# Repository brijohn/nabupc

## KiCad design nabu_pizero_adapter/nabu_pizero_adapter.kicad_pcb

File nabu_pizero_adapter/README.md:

# Description
This is a carrier board designed for a Raspberry Pi Zero W. It was made to fit in the empty case of an nabu network cable adapter and host a NABU Network Emulator allowing your nabu to request and load software.

The uses a MAX3070 to produce a RS422 signal from the PI's TTL UART and has a super capacitor based UPS to allow the pi time to cleanly shutdown in the event of a power loss. It has has a header that the front panel LEDS can be connected to and then controlled by the PI.

# Setup
In addition to this board you will also need a Raspberry PI Zero W. Though a suitable alternative is the bananapi M2 Zero, which has the same pinout and form factor, it also includes a U.FL connector for an external antenna, whereas the raspberry pi needs to modified.

The external antenna can be mounted in the existing F type connector hole in the back of the case, though since an SMA connector is smaller then an F type you will need a couple of washers on each side of the antenna's SMA connector to mount it.

The code used with the ATTiny85 to monitor the power status and report it to the PI over I2C was written by Scott M. Baker and can be found at https://github.com/sbelectronics/ups/.

# BOM

|         Item        |     Reference     | Quantity |             Digikey              |
|---------------------|-------------------|----------|----------------------------------|
|  0.1uf Capacitor    |  C3, C4, C5, C6   |     4    |          490-9197-1-ND           |
| 50F Super-capacitor |      C1, C2       |     2    |          1182-1051-ND            |
|    1N5820 Diode     |      D1, D3       |     2    |      112-1N5820-E3/73CT-ND       |
|   5.6V Zener Diode  |        D2         |     1    |         1N4734AFSCT-ND           |
|   5.1V Zener Diode  |        D4         |     1    |         1N4733AFSCT-ND           |
|      1A Fuse        |        F1         |     1    |             F2313-ND             |
|  Single Row Headers |    J3, J4, J5     |     1    |          S1012EC-40-ND           |
|      5-pin DIN      |        J2         |     1    |            CP-2350-ND            |
|    180 Resistor     |        R1         |     1    |     13-MFR-25FTE52-180RCT-ND     |
|    220 Resistor     | R9, R10, R11, R12 |     4    |             220QBK-ND            |
|    1k Resistor      |      R3, R4       |     2    |             1.0KQBK-ND           |
|   7.5k Resistor     |      R6, R8       |     2    |             7.5KQBK-ND           |
|   10k Resistor      |      R5, R7       |     2    |      13-CFR-25JT-52-10KCT-ND     |
|   2.2 3W Resistor   |        R2         |     1    |            A138434CT-ND          |
|      ATtiny85V      |        U3         |     1    |         ATTINY85V-10PU-ND        |
|       MAX3070       |        U1         |     1    |          MAX3070EEPD+-ND         |
|   Shunt Regulator   |      U5, U6       |     2    |            296-50325-ND          |
|       ULN2803A      |        U2         |     1    |            497-2356-5-ND         |
|      5V Step-Up     |        U4         |     1    | 2183-2891-ND, S7037-ND, S7038-ND |

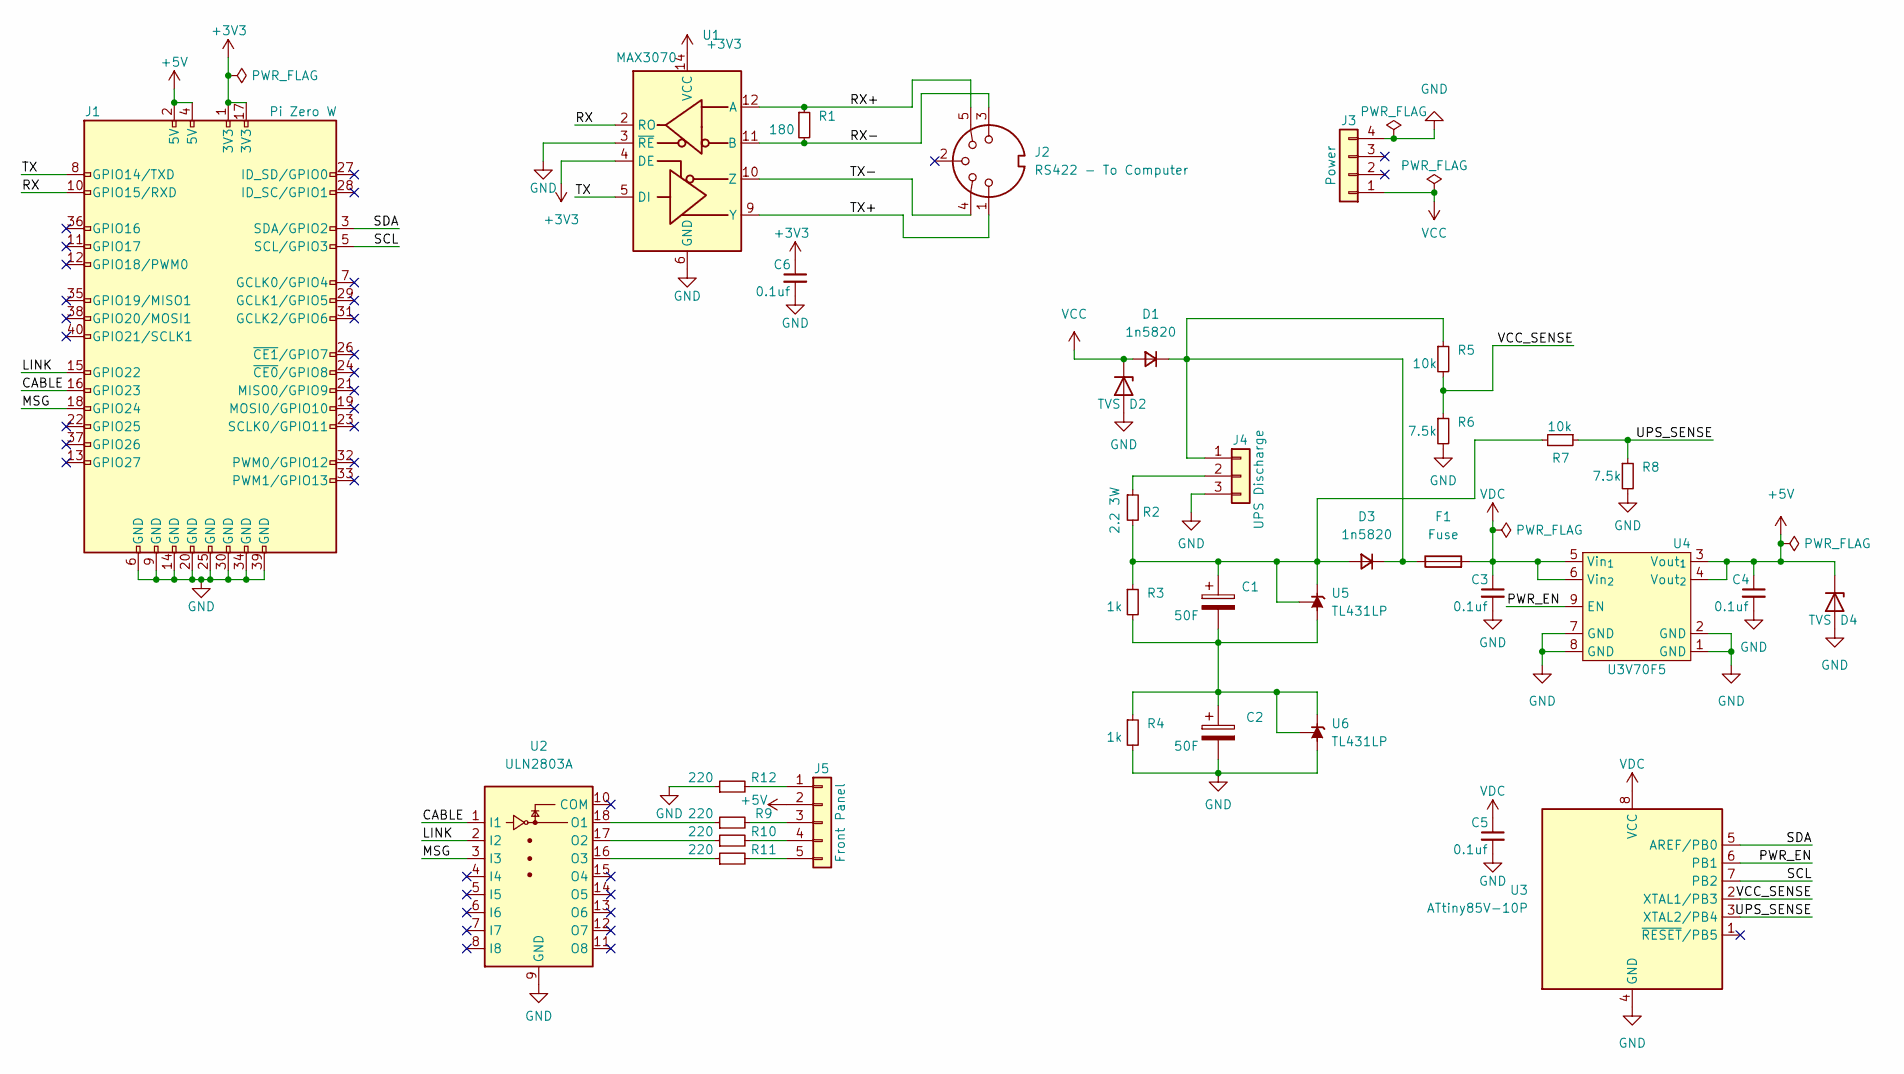
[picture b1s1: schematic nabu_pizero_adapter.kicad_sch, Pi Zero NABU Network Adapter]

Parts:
C1, C2: 50F; CP_Radial_D18.0mm_P7.50mm; Digi-Key 1182-1051-ND
C3, C4, C5, C6: 0.1uf; C_Disc_D5.0mm_W2.5mm_P2.50mm; Digi-Key 490-9197-1-ND
D1, D3: 1n5820; D_DO-201AD_P15.24mm_Horizontal; Digi-Key 112-1N5820-E3/73CT-ND
D2: TVS; D_DO-41_SOD81_P10.16mm_Horizontal; Digi-Key 1N4734AFSCT-ND
D4: TVS; D_DO-41_SOD81_P10.16mm_Horizontal; Digi-Key 1N4733AFSCT-ND
F1: Fuse; 0251001.MXL; Digi-Key F2313-ND
J1: Pi Zero W; Raspberry_Pi_Zero_Socketed_THT_MountingHoles; Digi-Key 1988-1063-ND
J2: RS422 - To Computer; CUI_SDS-50J; Digi-Key CP-2350-ND
J3: Power; PinHeader_1x04_P2.54mm_Vertical; Digi-Key S1012EC-40-ND
J4: UPS Discharge; PinHeader_1x03_P2.54mm_Vertical
J5: Front Panel; PinHeader_1x05_P2.54mm_Vertical
R1: 180; R_Axial_DIN0207_L6.3mm_D2.5mm_P10.16mm_Horizontal; Digi-Key 13-MFR-25FTE52-180RCT-ND
R2: 2.2 3W; R_Axial_DIN0516_L15.5mm_D5.0mm_P20.32mm_Horizontal; Digi-Key A138434CT-ND
R3, R4: 1k; R_Axial_DIN0207_L6.3mm_D2.5mm_P10.16mm_Horizontal; Digi-Key 1.0KQBK-ND
R5, R7: 10k; R_Axial_DIN0207_L6.3mm_D2.5mm_P10.16mm_Horizontal; Digi-Key 13-CFR-25JT-52-10KCT-ND
R6, R8: 7.5k; R_Axial_DIN0207_L6.3mm_D2.5mm_P10.16mm_Horizontal; Digi-Key 7.5KQBK-ND
R9, R10, R11, R12: 220; R_Axial_DIN0207_L6.3mm_D2.5mm_P10.16mm_Horizontal; Digi-Key 220QBK-ND
U1: MAX3070; DIP-14_W7.62mm; Digi-Key MAX3070EEPD+-ND
U2: ULN2803A; DIP-18_W7.62mm; Digi-Key 497-2356-5-ND
U3: ATtiny85V-10P; DIP-8_W7.62mm_Socket; Digi-Key ATTINY85V-10PU-ND
U4: U3V70F5; Digi-Key 2183-2891-ND, S7037-ND, S7038-ND
U5, U6: TL431LP; TO-92_Inline; Digi-Key 296-50325-ND

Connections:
+3V3: C6.1, J1.1 (3V3), J1.17 (3V3), U1.4 (DE), U1.14 (VCC)
+5V: C4.1, D4.1 (K), J1.2 (5V), J1.4 (5V), J5.2, U4.3 (Vout_{1}), U4.4 (Vout_{2})
/CABLE: J1.16 (GPIO23), U2.1 (I1)
/LINK: J1.15 (GPIO22), U2.2 (I2)
/MSG: J1.18 (GPIO24), U2.3 (I3)
/PWR_EN: U3.6 (PB1), U4.9 (EN)
/RX: J1.10 (GPIO15/RXD), U1.2 (RO)
/RX+: J2.5, R1.1, U1.12 (A)
/RX-: J2.3, R1.2, U1.11 (B)
/SCL: J1.5 (SCL/GPIO3), U3.7 (PB2)
/SDA: J1.3 (SDA/GPIO2), U3.5 (AREF/PB0)
/TX: J1.8 (GPIO14/TXD), U1.5 (DI)
/TX+: J2.1, U1.9 (Y)
/TX-: J2.4, U1.10 (Z)
/UPS_SENSE: R7.1, R8.1, U3.3 (XTAL2/PB4)
/VCC_SENSE: R5.2, R6.1, U3.2 (XTAL1/PB3)
GND: C2.2, C3.2, C4.2, C5.2, C6.2, D2.2 (A), D4.2 (A), J1.6 (GND), J1.9 (GND), J1.14 (GND), J1.20 (GND), J1.25 (GND), J1.30 (GND), J1.34 (GND), J1.39 (GND), J3.4, J4.3, R4.2, R6.2, R8.2, R12.1, U1.3 (~RE), U1.6 (GND), U1.7 (GND), U2.9 (GND), U3.4 (GND), U4.1 (GND), U4.2 (GND), U4.7 (GND), U4.8 (GND), U6.2 (A)
unnamed: C1.1, D3.2 (A), R2.2, R3.1, R7.2, U5.1 (REF), U5.3 (K)
unnamed: C1.2, C2.1, R3.2, R4.1, U5.2 (A), U6.1 (REF), U6.3 (K)
unnamed: D1.1 (K), D3.1 (K), F1.1, J4.1, R5.1
unnamed: J4.2, R2.1
unnamed: J5.1, R12.2
unnamed: J5.3, R9.2
unnamed: J5.4, R10.2
unnamed: J5.5, R11.2
unnamed: R9.1, U2.18 (O1)
unnamed: R10.1, U2.17 (O2)
unnamed: R11.1, U2.16 (O3)
VCC: D1.2 (A), D2.1 (K), J3.1
VDC: C3.1, C5.1, F1.2, U3.8 (VCC), U4.5 (Vin_{1}), U4.6 (Vin_{2})

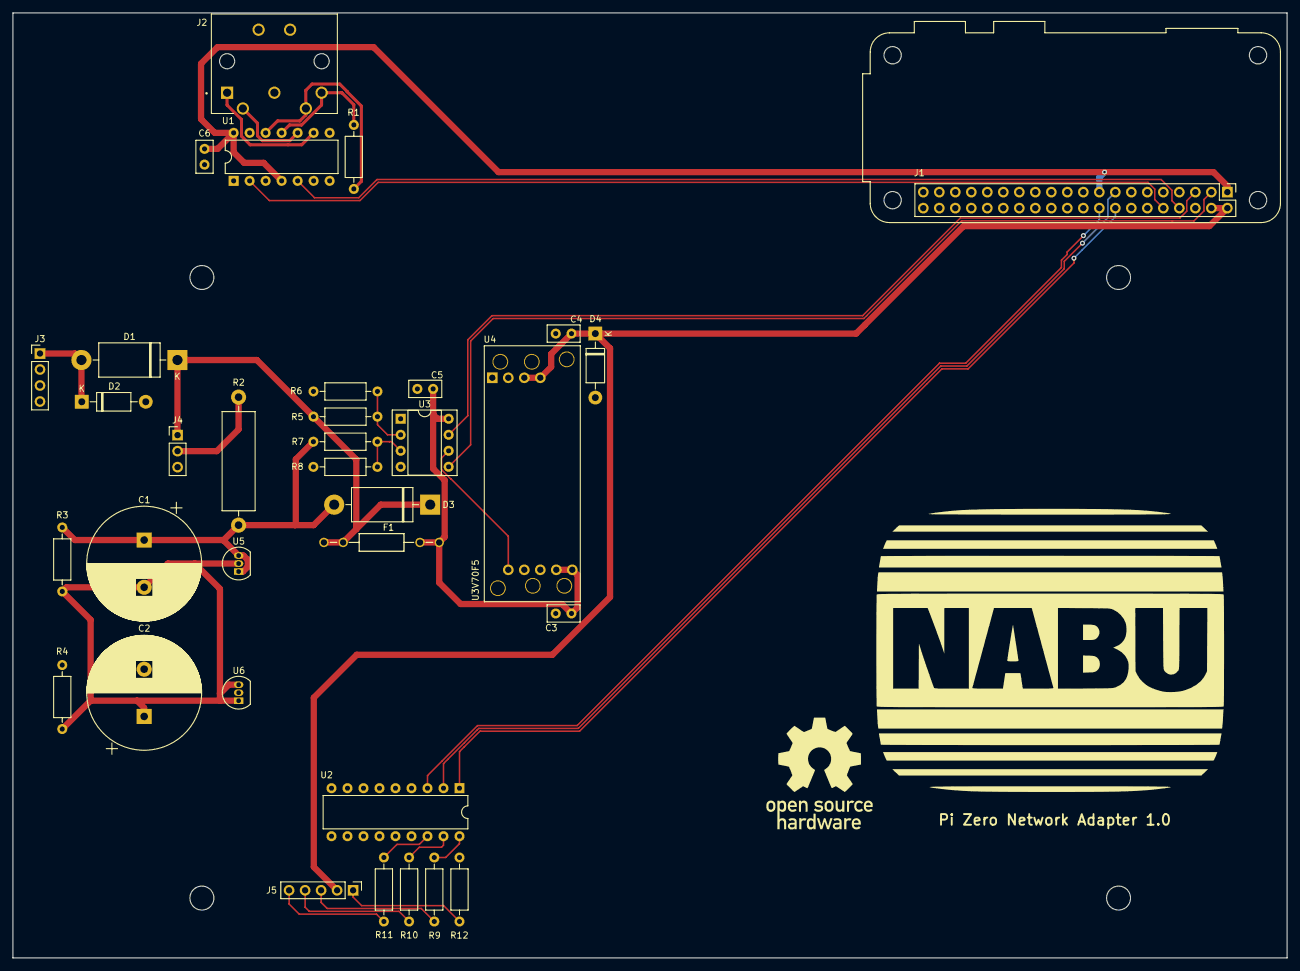
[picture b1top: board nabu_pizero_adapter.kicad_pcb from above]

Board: 2 copper layers, 202.2 x 150.0 mm, 40 parts (0 on the bottom side), 30 nets.

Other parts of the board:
G1: LOGO; nabu_logo
G2: LOGO; osw_logo
H1, H2, H3, H4: MountingHole_3.2mm_M3

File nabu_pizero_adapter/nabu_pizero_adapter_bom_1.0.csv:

Component,Description,References,Value,Quantity Per PCB,Digi-Key,MFN
1,"Unpolarized capacitor, small symbol",C3 C4 C5 C6,0.1uf,4,490-9197-1-ND,RDER72A104K1S1H03A
2,Polarized capacitor,C1 C2,50F,2,1182-1051-ND,BCAP0050 P270 X01
3,"Diode, small symbol",D1 D3,1n5820,2,112-1N5820-E3/73CT-ND,1N5820-E3/73
4,Zener diode,D2 D4,TVS,2,1N4734AFSCT-ND 1N4733AFSCT-ND,1N4734ATR 1N4733ATR
5,Fuse,F1,Fuse,1,F2313-ND,0251001.MXL
6,"Generic connector, single row, 01x03, script generated (kicad-library-utils/schlib/autogen/connector/)",J4,Conn_01x03,1,,
7,"Generic connector, single row, 01x05, script generated (kicad-library-utils/schlib/autogen/connector/)",J5,Front Panel,1,,
8,"Generic connector, single row, 01x04, script generated (kicad-library-utils/schlib/autogen/connector/)",J3,Power,1,S1012EC-40-ND,PREC040SAAN-RC
9,5-pin DIN connector (5-pin DIN-5 stereo),J2,RS422 - To Computer,1,CP-2350-ND,SDS-50J
10,"Resistor, small symbol",R1,180,1,13-MFR-25FTE52-180RCT-ND,MFR-25FTE52-180R
11,"Resistor, small symbol",R9 R10 R11 R12,220,4,220QBK-ND,CFR-25JB-52-220R
12,"Resistor, small symbol",R3 R4,1k,2,1.0KQBK-ND,CFR-25JB-52-1K
13,"Resistor, small symbol",R6 R8,7.5k,2,7.5KQBK-ND,CFR-25JB-52-7K5
14,"Resistor, small symbol",R5 R7,10k,2,13-CFR-25JT-52-10KCT-ND,CFR-25JT-52-10K
15,"Resistor, small symbol",R2,2.2 3W,1,A138434CT-ND,RR03J2R2TB
16,"10MHz, 8kB Flash, 512B SRAM, 512B EEPROM, debugWIRE, DIP-8",U3,ATtiny85V-10P,1,ATTINY85V-10PU-ND,ATTINY85V-10PU
17,"RS-485, RS-422 Full duplex 250kbps transceiver, DIP-14",U1,MAX3070,1,MAX3070EEPD+-ND,MAX3070EEPD+
18,"Shunt Regulator, TO-92",U5 U6,TL431LP,2,296-50325-ND,TL431AILPE3
19,Polou 5V Step-Up Converter,U4,U3V70F5,1,"2183-2891-ND, S7037-ND, S7038-ND",2891
20,"Darlington Transistor Arrays, SOIC18/DIP18",U2,ULN2803A,1,497-2356-5-ND,ULN2803A





Component Groups:,20
Component Count:,33
Fitted Components:,33
Number of PCBs:,1
Total components:,33
Schematic Version:,1.0
Schematic Date:,2023-05-30
PCB Variant:,default
BoM Date:,Tue 30 May 2023 06:34:02 PM EDT
Schematic Source:,nabu_pizero_adapter.kicad_sch
KiCad Version:,Eeschema 6.0.2+dfsg-1

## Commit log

2023-05-24 Add HDD coldboot and ldrbios assembly code
2023-05-24 Add relocatable crt0 for use with NABU-LIB
2023-05-31 Add pizero adapter board
2023-11-27 Add latex documentation for nabu paddles
2023-11-27 Basic Breakout game using paddle controllers
2023-12-16 Add paddle based version of pong
2023-12-27 Add a wrapper to allow the MSX version of riverraid to be played on the nabu
2023-12-28 Fix graphical glitches on riverraid port
2024-01-07 Allow riverraid to be compiled as a .com file for CP/M
2024-01-07 Add Arkanoid conversion includes paddle support
2024-01-18 Add Choplifter MSX conversion
2024-01-18 Update arkanoid readme
2024-02-14 Add initial MSX conversion framework
2024-02-14 Add more generalized mode 2 init support to CBIOS
2024-02-14 add setmlt to cbios
2024-02-27 Add cbios functions: setrd, rdvrm, gtstck, and gttrig
2024-03-01 Update splash screen
2024-03-01 Add support for building CP/M .com files
2024-03-01 Add bomberman and thexder conversions
2024-03-01 Add readme.md to libmsx
2024-03-01 Add License/Copyright information
2024-03-03 Reorder cbios patches
2024-03-09 Add Hyper Rally and Roadfighter to MSX converstions
2024-03-09 Save/restore all registers in keyboard irq
2024-03-09 Add .gitignore file
2024-03-19 Add support for two joysticks to libmsx
2024-03-19 Implement chgmod, chsns and chget in libmsx
2024-03-19 Add support for TIMI Hook in libmsx
2024-04-07 Fix libmsx bug in handling of special keys
2024-04-07 Add boulderdash conversion
2024-04-07 Update libmsx keyboard interrupt to store ascii keys in KEYBUF
2024-04-16 Fix bug in gttrig when handling button 2
2024-04-16 Add Elevator Action conversion to libmsx
2024-04-22 Add H.E.R.O MSX conversion
2024-05-13 Remove whitespace from end of line
2024-05-13 Add missing double quotes
    Fixes #2
2024-11-16 allow setting irq_mask per rom in libmsx
2024-11-16 Add galaga conversion to libmsx
2024-11-16 Support two button joystick in libmsx
2024-11-16 Add support for two button joystick to choplifter
2024-12-02 Add ColecoVision ROM Loader
2025-04-23 Added Joust patches
2025-04-23 Update patches.z80 changed kp_switch to RST 10
2025-04-24 not required
    data not code
2025-04-24 Added Joust patches (#4)
    * Added Joust patches
    * Update patches.z80 changed kp_switch to RST 10
    * Not required - data not code
2025-04-27 Joystick 1 and 2 reading was backwards for Joust
    Fixed Joust Joystick 1 and 2 reading and code cleanup
2025-04-30 Changed joystick switching to automatic
2025-04-30 alignment
2025-08-31 nabu_coleco: Update emulation vector to address 0x2100
2025-09-08 nabu_coleco: Add menu to select which ROM to load
2025-10-23 nabu_coleco: add linker script for menu
